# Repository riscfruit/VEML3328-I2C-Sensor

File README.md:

# VEML3328-I2C-Sensor
Riscfruit Vishay VEML3328 Color I2C sensor module

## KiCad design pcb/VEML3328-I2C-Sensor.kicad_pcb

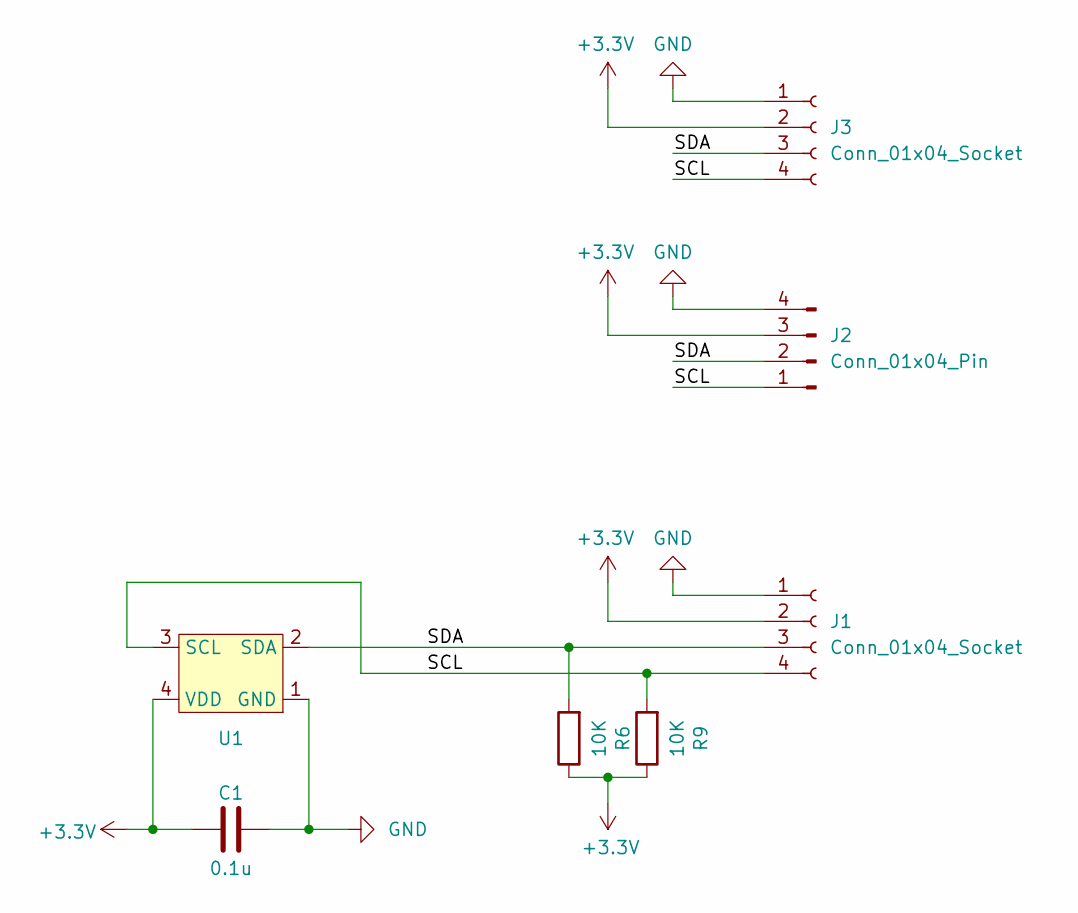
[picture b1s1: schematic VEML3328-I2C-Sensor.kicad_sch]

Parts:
C1: 0.1u; C_0402_1005Metric
J1, J3: Conn_01x04_Socket; JST_SH_SM04B-SRSS-TB_1x04-1MP_P1.00mm_Horizontal
J2: Conn_01x04_Pin; PinHeader_1x04_P2.54mm_Vertical
R6, R9: 10K; R_0402_1005Metric
U1: SENSOR-SMD_VEML3328

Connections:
+3.3V: C1.1, J1.2, J2.3, J3.2, R6.1, R9.1, U1.4 (VDD)
/SCL: J1.4, J2.1, J3.4, R9.2, U1.3 (SCL)
/SDA: J1.3, J2.2, J3.3, R6.2, U1.2 (SDA)
GND: C1.2, J1.1, J2.4, J3.1, U1.1 (GND)

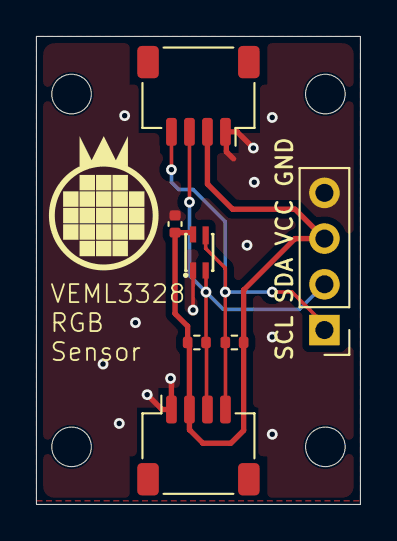
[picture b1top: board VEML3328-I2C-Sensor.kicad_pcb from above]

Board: 2 copper layers, 18.0 x 26.0 mm, 11 parts (0 on the bottom side), 4 nets.

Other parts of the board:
H1, H1#2, H1#3, H1#4: MountingHole; MountingHole_2.2mm_M2
